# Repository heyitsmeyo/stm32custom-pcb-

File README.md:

# stm32custom-pcb-
a custom stm32 pcb design 

# if you like the project , you can donate us for more : 

    https://ko-fi.com/heyitsmeyo

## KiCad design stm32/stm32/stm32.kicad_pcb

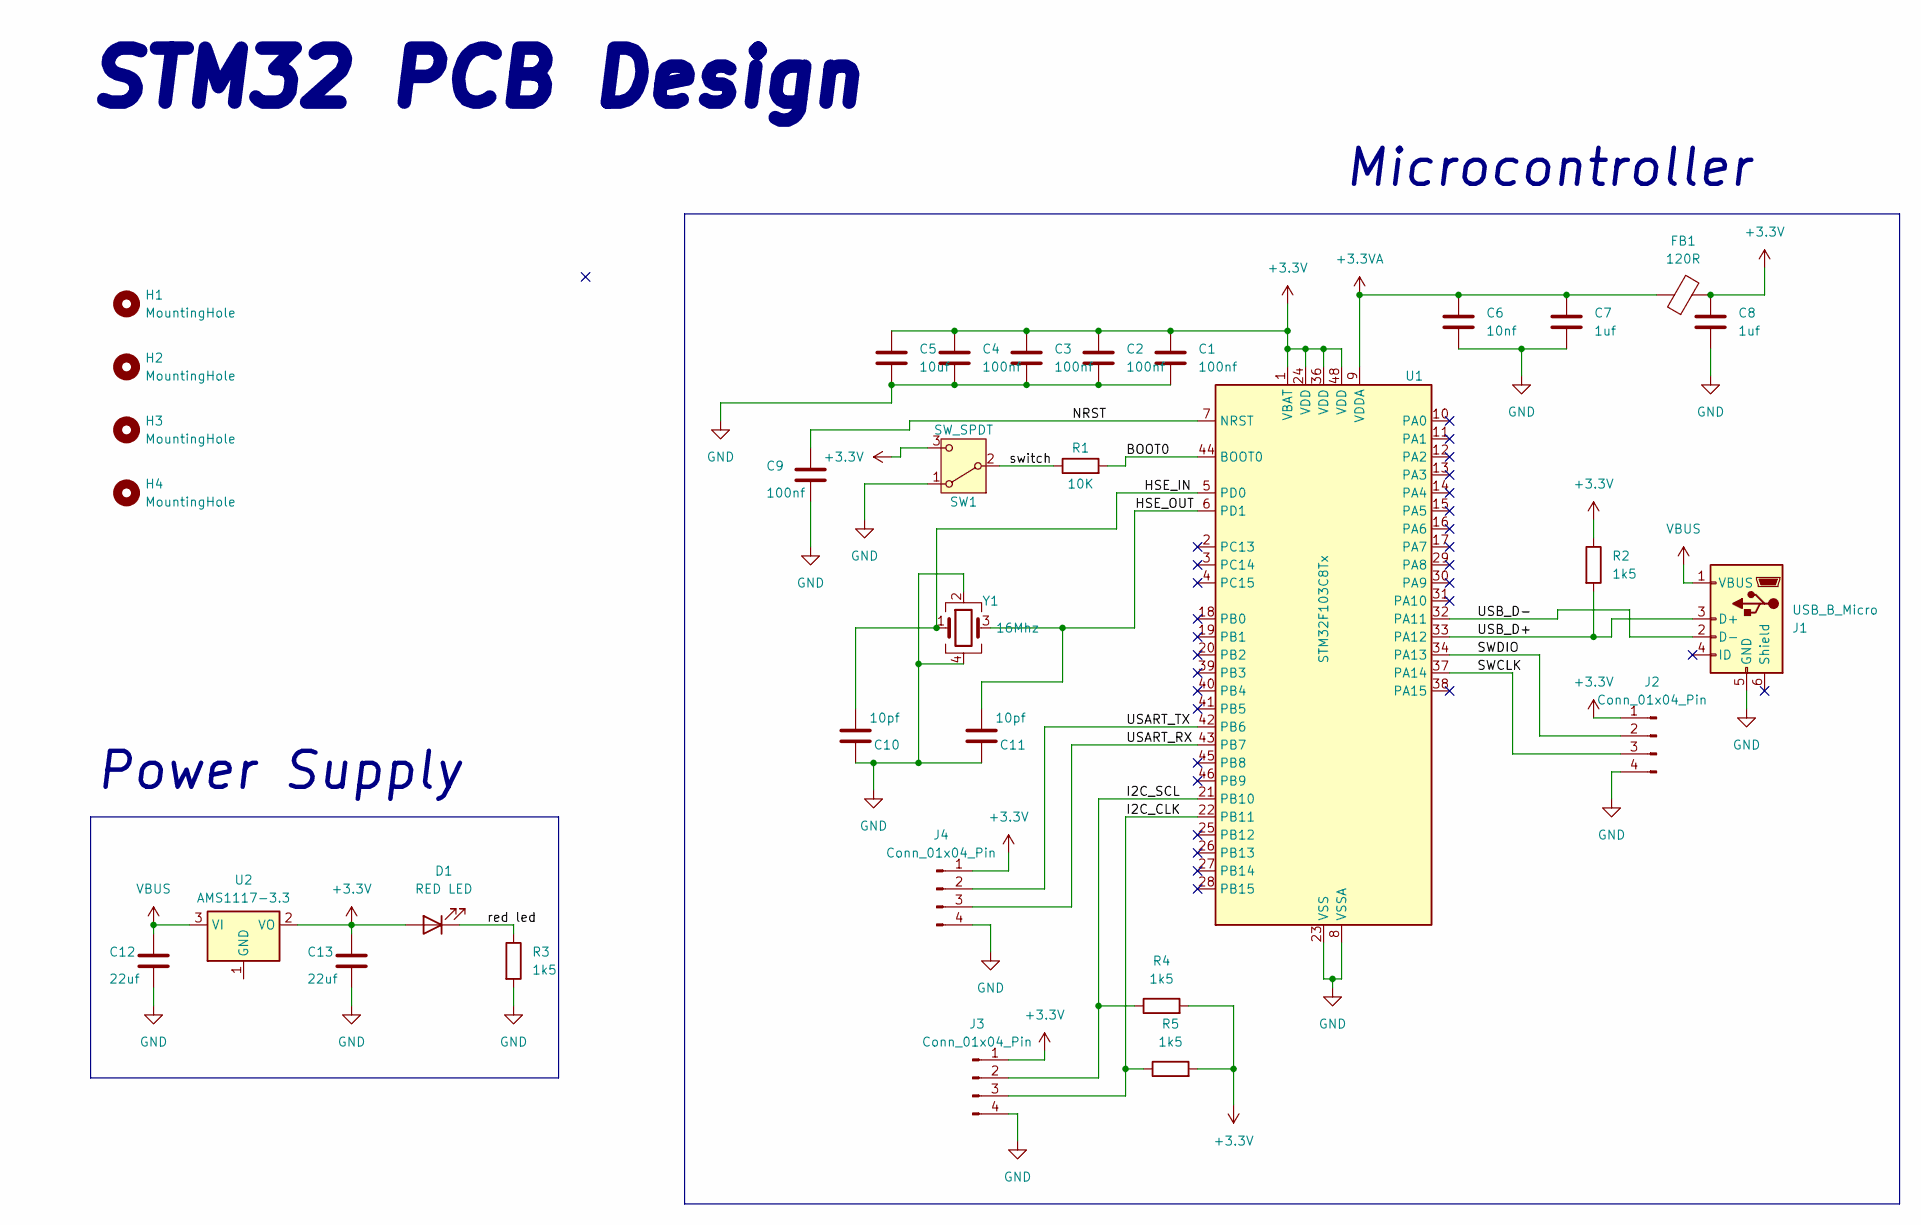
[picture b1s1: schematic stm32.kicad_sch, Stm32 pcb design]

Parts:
C1, C2, C3, C4: 100nf; C_0402_1005Metric
C5: 10uf; C_0402_1005Metric
C6: 10nf; C_0402_1005Metric
C7, C8: 1uf; C_0201_0603Metric
C9: 100nf; C_0603_1608Metric
C10, C11: 10pf; C_0805_2012Metric
C12, C13: 22uf; C_0805_2012Metric
D1: RED LED; LED_0201_0603Metric
FB1: 120R; L_0603_1608Metric
H1, H2, H3, H4: MountingHole; MountingHole_2.1mm
J1: USB_B_Micro; USB_Micro-B_Wuerth_629105150521
J2, J3, J4: Conn_01x04_Pin; PinSocket_1x04_P2.54mm_Vertical
R1: 10K; R_0805_2012Metric
R2, R3, R4, R5: 1k5; R_0805_2012Metric
SW1: SW_SPDT; SW_SPDT_PCM12
U1: STM32F103C8Tx; LQFP-48_7x7mm_P0.5mm
U2: AMS1117-3.3; SOT-223-3_TabPin2
Y1: 16Mhz; Crystal_SMD_3225-4Pin_3.2x2.5mm

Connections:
+3.3V: C1.1, C2.1, C3.1, C4.1, C5.2, C8.2, C13.1, D1.2 (A), FB1.2, J2.1, J3.1, J4.1, R2.1, R4.2, R5.2, SW1.3 (C), U1.1 (VBAT), U1.24 (VDD), U1.36 (VDD), U1.48 (VDD), U2.2 (VO)
+3.3VA: C6.2, C7.2, FB1.1, U1.9 (VDDA)
/BOOT0: R1.2, U1.44 (BOOT0)
/HSE_IN: C10.2, U1.5 (PD0), Y1.1
/HSE_OUT: C11.2, U1.6 (PD1), Y1.3
/I2C_CLK: J3.3, R5.1, U1.22 (PB11)
/I2C_SCL: J3.2, R4.1, U1.21 (PB10)
/NRST: C9.1, U1.7 (NRST)
/SWCLK: J2.3, U1.37 (PA14)
/SWDIO: J2.2, U1.34 (PA13)
/USART_RX: J4.3, U1.43 (PB7)
/USART_TX: J4.2, U1.42 (PB6)
/USB_D+: J1.3 (D+), R2.2, U1.33 (PA12)
/USB_D-: J1.2 (D-), U1.32 (PA11)
/red led: D1.1 (K), R3.1
/switch: R1.1, SW1.2 (B)
GND: C1.2, C2.2, C3.2, C4.2, C5.1, C6.1, C7.1, C8.1, C9.2, C10.1, C11.1, C12.2, C13.2, J1.5 (GND), J2.4, J3.4, J4.4, R3.2, SW1.1 (A), U1.8 (VSSA), U1.23 (VSS), U1.35 (VSS), U1.47 (VSS), Y1.2, Y1.4
VBUS: C12.1, J1.1 (VBUS), U2.3 (VI)

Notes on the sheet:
STM32 PCB Design
Power Supply
Microcontroller

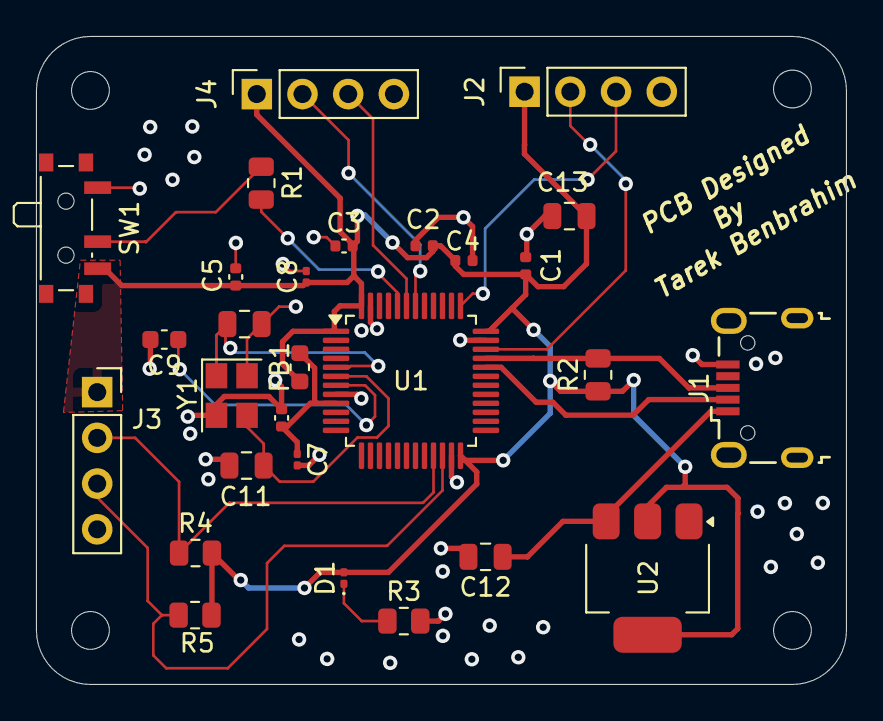
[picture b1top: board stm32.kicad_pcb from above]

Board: 4 copper layers, 45.0 x 36.0 mm, 32 parts (0 on the bottom side), 18 nets.
